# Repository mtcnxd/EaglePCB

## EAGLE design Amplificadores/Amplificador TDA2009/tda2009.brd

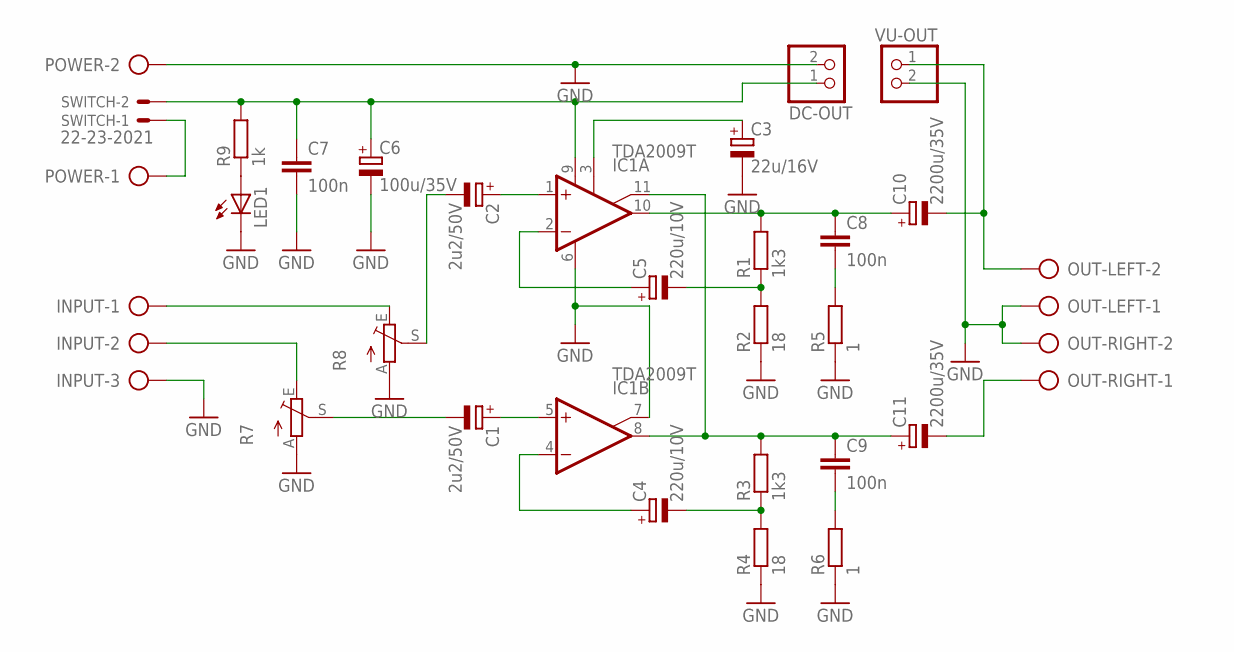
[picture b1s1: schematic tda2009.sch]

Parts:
C1, C2: 2u2/50V; E2,5-5
C3: 22u/16V; E2,5-5
C4, C5: 220u/10V; E2,5-6
C6: 100u/35V; E3,5-8
C7, C8, C9: 100n; C025-025X050
C10, C11: 2200u/35V; E7,5-16
DC-OUT: PINHD-1X2; 1X02
IC1: TDA2009T; SIP11
INPUT: AK300/3
LED1: LED5MM
OUT-LEFT: AK300/2
OUT-RIGHT: AK300/2
POWER: AK300/2
R1, R3: 1k3; 0207/10
R2, R4: 18; 0207/10
R5, R6: 1; 0207/10
R7, R8: TRIM_EU-RJ9W; RJ9W
R9: 1k; 0207/10
SWITCH: 22-23-2021
VU-OUT: PINHD-1X2; 1X02

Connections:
GND: C3.-, C6.-, C7.2, DC-OUT.2, IC1.6 (GND), IC1.7 (BTSP), INPUT.3, LED1.K (C), OUT-LEFT.1, OUT-RIGHT.2, POWER.2, R2.1, R4.1, R5.1, R6.1, R7.A, R8.A, VU-OUT.2
unnamed: C5.-, R1.1, R2.2
unnamed: C4.-, R3.1, R4.2
unnamed: C8.2, R5.2
unnamed: C9.2, R6.2
unnamed: C9.1, C11.+, IC1.8 (OUT), IC1.11 (BTSP), R3.2
unnamed: C8.1, C10.+, IC1.10 (OUT), R1.2
unnamed: C1.+, IC1.5 (+IN)
unnamed: C2.+, IC1.1 (+IN)
unnamed: INPUT.2, R7.E
unnamed: C3.+, IC1.3 (SVRR)
unnamed: C5.+, IC1.2 (-IN)
unnamed: C4.+, IC1.4 (-IN)
unnamed: INPUT.1, R8.E
unnamed: C1.-, R7.S
unnamed: C10.-, OUT-LEFT.2, VU-OUT.1
unnamed: C11.-, OUT-RIGHT.1
unnamed: C2.-, R8.S
unnamed: LED1.A, R9.1
unnamed: POWER.1, SWITCH.1
unnamed: C6.+, C7.1, DC-OUT.1, IC1.9 (V+), R9.2, SWITCH.2

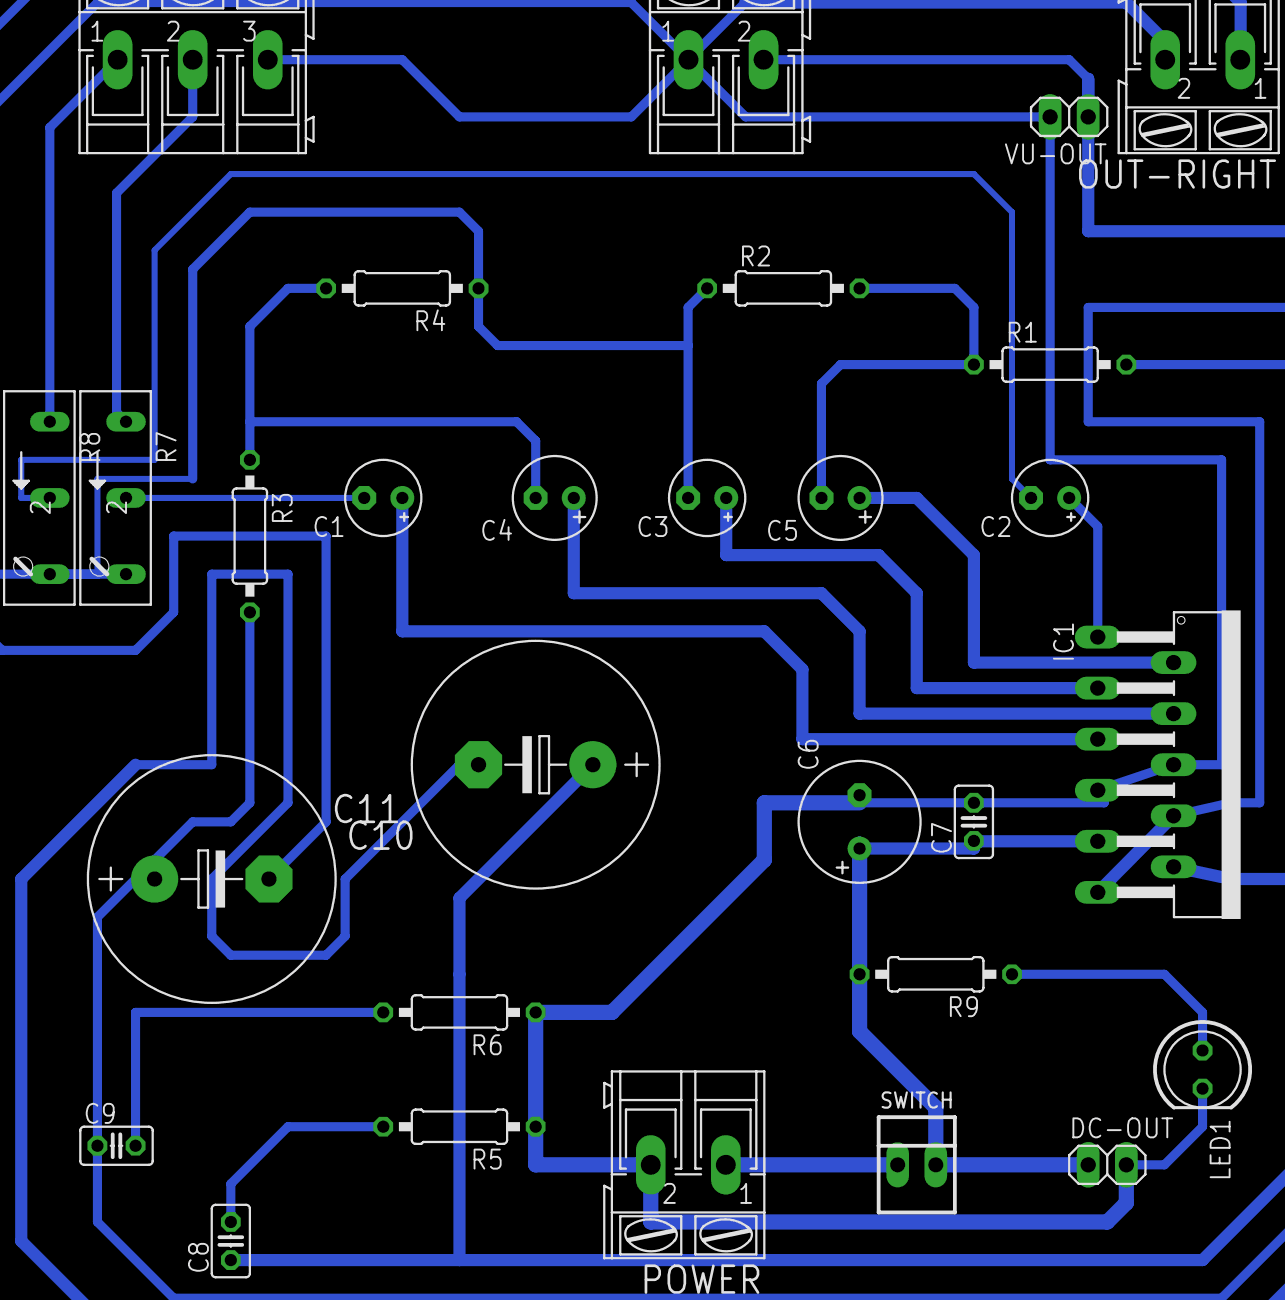
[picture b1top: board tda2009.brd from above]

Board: 2 copper layers, 29 parts (0 on the bottom side), 21 nets.

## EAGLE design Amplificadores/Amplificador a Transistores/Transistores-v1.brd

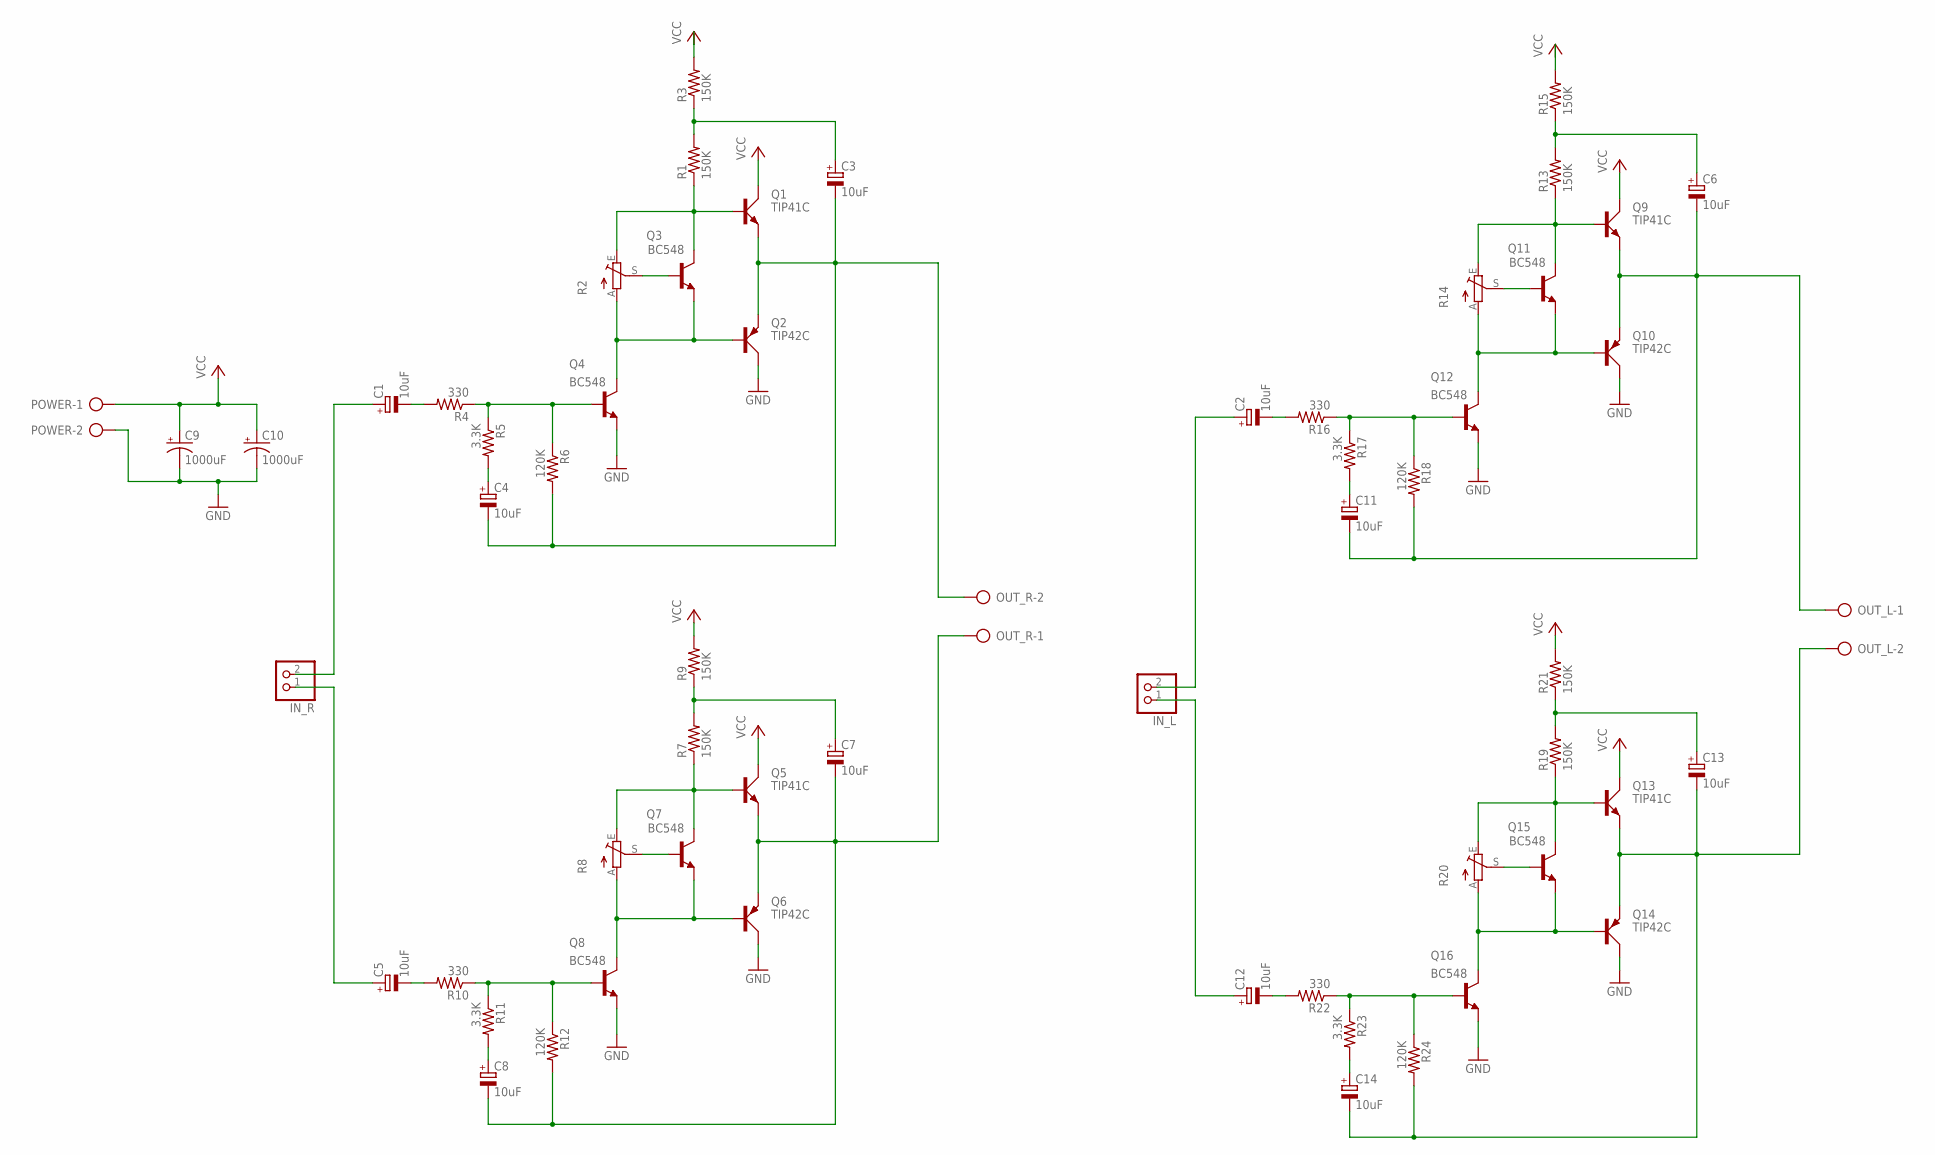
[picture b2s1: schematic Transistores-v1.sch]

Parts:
C1, C2, C3, C4, C5, C6, C7, C8, C11, C12, C13, C14: 10uF; E2,5-5
C9, C10: 1000uF; E2,5-7
IN_L: PINHD-1X2; 1X02
IN_R: PINHD-1X2; 1X02
OUT_L: AK300/2
OUT_R: AK300/2
POWER: AK300/2
Q1, Q5, Q9, Q13: TIP41C; TO220AV
Q2, Q6, Q10, Q14: TIP42C; TO220AV
Q3, Q4, Q7, Q8, Q11, Q12, Q15, Q16: BC548; TO92-EBC
R1, R3, R7, R9, R13, R15, R19, R21: 150K; 0204/7
R2, R8, R14, R20: TRIM_EU-LI10; LI10
R4, R10, R16, R22: 330; 0204/7
R5, R11, R17, R23: 3.3K; 0204/7
R6, R12, R18, R24: 120K; 0204/7

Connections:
GND: C9.-, C10.-, POWER.2, Q2.C, Q4.E, Q6.C, Q8.E, Q10.C, Q12.E, Q14.C, Q16.E
unnamed: Q3.B, R2.S
unnamed: Q1.B, Q3.C, R1.1, R2.E
unnamed: Q2.B, Q3.E, Q4.C, R2.A
unnamed: Q7.B, R8.S
unnamed: C1.+, IN_R.2
unnamed: C3.+, R1.2, R3.1
unnamed: Q4.B, R4.1, R5.1, R6.1
unnamed: C1.-, R4.2
unnamed: C4.+, R5.2
unnamed: C3.-, C4.-, OUT_R.2, Q1.E, Q2.E, R6.2
unnamed: Q5.B, Q7.C, R7.1, R8.E
unnamed: Q6.B, Q7.E, Q8.C, R8.A
unnamed: C7.+, R7.2, R9.1
unnamed: C5.+, IN_R.1
unnamed: Q8.B, R10.1, R11.1, R12.1
unnamed: C5.-, R10.2
unnamed: C8.+, R11.2
unnamed: C7.-, C8.-, OUT_R.1, Q5.E, Q6.E, R12.2
unnamed: Q11.B, R14.S
unnamed: Q9.B, Q11.C, R13.1, R14.E
unnamed: Q10.B, Q11.E, Q12.C, R14.A
unnamed: C6.+, R13.2, R15.1
unnamed: Q12.B, R16.1, R17.1, R18.1
unnamed: C2.-, R16.2
unnamed: C11.+, R17.2
unnamed: C6.-, C11.-, OUT_L.1, Q9.E, Q10.E, R18.2
unnamed: Q15.B, R20.S
unnamed: Q13.B, Q15.C, R19.1, R20.E
unnamed: Q14.B, Q15.E, Q16.C, R20.A
unnamed: C13.+, R19.2, R21.1
unnamed: Q16.B, R22.1, R23.1, R24.1
unnamed: C12.-, R22.2
unnamed: C14.+, R23.2
unnamed: C13.-, C14.-, OUT_L.2, Q13.E, Q14.E, R24.2
unnamed: C2.+, IN_L.2
unnamed: C12.+, IN_L.1
VCC: C9.+, C10.+, POWER.1, Q1.C, Q5.C, Q9.C, Q13.C, R3.2, R9.2, R15.2, R21.2

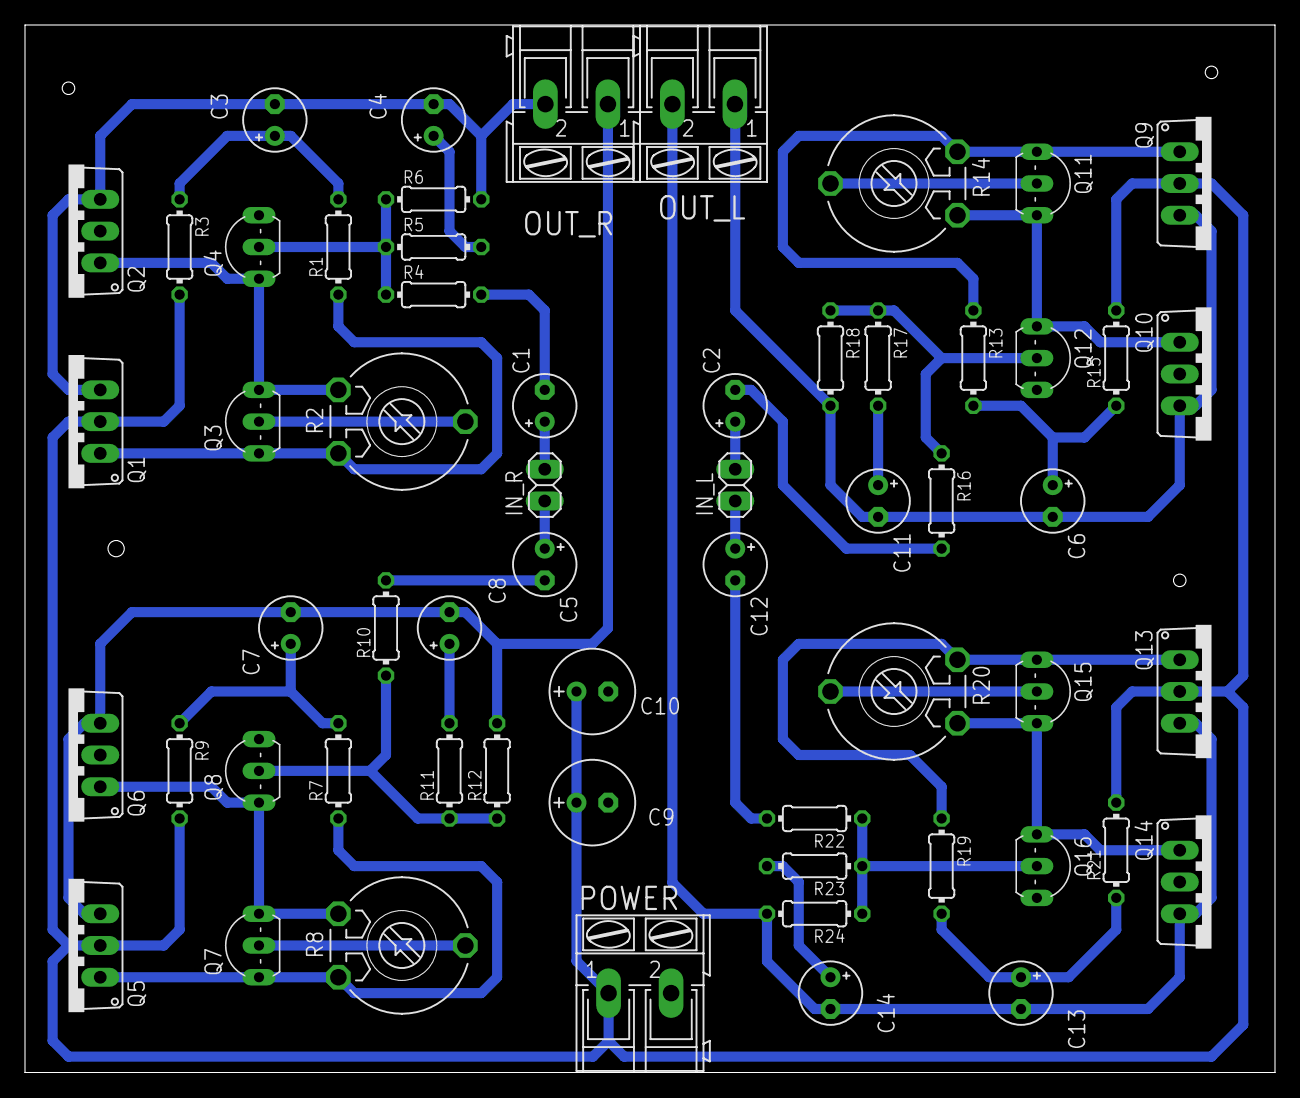
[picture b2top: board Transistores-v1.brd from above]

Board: 2 copper layers, 100.0 x 83.8 mm, 59 parts (0 on the bottom side), 38 nets.

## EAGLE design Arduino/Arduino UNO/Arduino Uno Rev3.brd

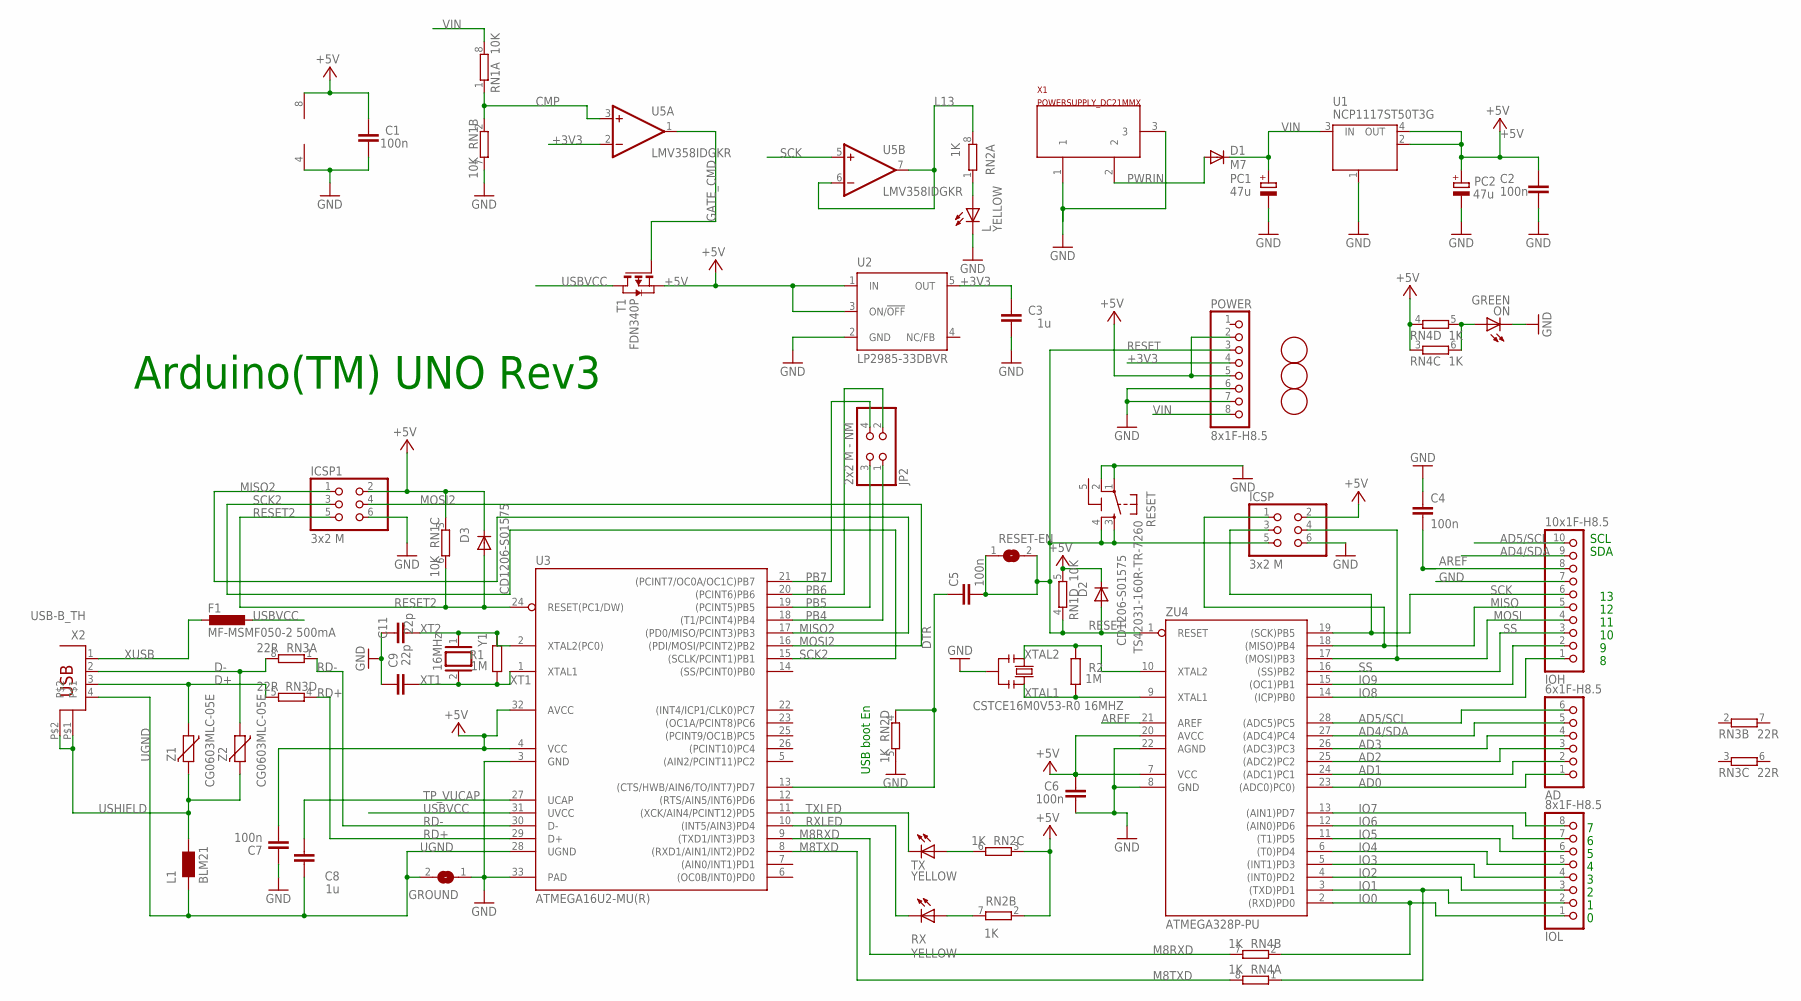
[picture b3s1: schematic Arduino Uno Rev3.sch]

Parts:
AD: 6x1F-H8.5; 1X06
C1, C2, C4, C5, C6, C7: 100n; C0603-ROUND
C3, C8: 1u; C0603-ROUND
C9, C11: 22p; C0603-ROUND
D1: M7; SMB
D2, D3: CD1206-S01575; MINIMELF
F1: MF-MSMF050-2 500mA; L1812
FD1, FD2, FD3: FIDUCIALMOUNT; FIDUCIA-MOUNT
GROUND: SJ
ICSP, ICSP1: 3x2 M; 2X03
IOH: 10x1F-H8.5; 1X10
IOL: 8x1F-H8.5; 1X08
JP2: 2x2 M - NM; 2X02
L: YELLOW; CHIP-LED0805
L1: BLM21; 0805
ON: GREEN; CHIP-LED0805
PC1, PC2: 47u; PANASONIC_D
POWER: 8x1F-H8.5; 1X08
R1, R2: 1M; R0603-ROUND
RESET: TS42031-160R-TR-7260; TS42
RESET-EN: SJ
RN1: 10K; CAY16
RN2, RN4: 1K; CAY16
RN3: 22R; CAY16
RX: YELLOW; CHIP-LED0805
T1: FDN340P; SOT-23
TX: YELLOW; CHIP-LED0805
U1: NCP1117ST50T3G; SOT223
U2: LP2985-33DBVR; SOT23-DBV
U3: ATMEGA16U2-MU(R); MLF32
U5: LMV358IDGKR; MSOP08
X1: POWERSUPPLY_DC21MMX; POWERSUPPLY_DC-21MM
X2: USB-B_TH; PN61729
Y1: 16MHz; QS
Y2: CSTCE16M0V53-R0 16MHZ; RESONATOR
Z1, Z2: CG0603MLC-05E; CT/CN0603
ZU4: ATMEGA328P-PU; DIL28-3

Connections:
5-GND: RESET.5 (5-GND)
+3V3: C3.2, POWER.4, U2.5 (OUT), U5.2 (-IN)
+5V: C1.2, C2.2, C6.2, C7.1, D2.C, D3.C, ICSP.2, ICSP1.2, PC2.+, POWER.2, POWER.5, RN1.3 (1), RN1.5 (2), RN2.2 (1), RN2.3 (1), RN4.3 (1), RN4.4 (1), T1.2 (S), U1.2 (OUT), U1.4 (OUT), U2.1 (IN), U2.3 (ON/!OFF), U3.4 (VCC), U3.32 (AVCC), U5.8 (V+), ZU4.7 (VCC), ZU4.20 (AVCC)
AD0: AD.1, ZU4.23 ((ADC0)PC0))
AD1: AD.2, ZU4.24 ((ADC1)PC1)
AD2: AD.3, ZU4.25 ((ADC2)PC2)
AD3: AD.4, ZU4.26 ((ADC3)PC3)
AD4/SDA: AD.5, IOH.9, ZU4.27 ((ADC4)PC4)
AD5/SCL: AD.6, IOH.10, ZU4.28 ((ADC5)PC5)
AREF: C4.2, IOH.8, ZU4.21 (AREF)
CMP: RN1.1, RN1.2 (1), U5.3 (+IN)
D+: RN3.5 (2), X2.3, Z1.1
D-: RN3.8 (2), X2.2, Z2.1
DTR: C5.1, RN2.4 (1), U3.13 ((CTS/HWB/AIN6/TO/INT7)PD7)
GATE_CMD: T1.3 (G), U5.1 (OUT)
GND: C1.1, C2.1, C3.1, C4.1, C6.1, C7.2, C9.2, C11.2, GROUND.1, ICSP.6, ICSP1.6, IOH.7, L.C, ON.C, PC1.-, PC2.-, POWER.6, POWER.7, RESET.1, RESET.2, RN1.7 (2), RN2.5 (2), U1.1 (GND/ADJ), U2.2 (GND), U3.3 (GND), U3.33 (PAD), U5.4 (V-), X1.1, X1.3, Y2.2, ZU4.8 (GND), ZU4.22 (AGND)
IO0: IOL.1, RN4.2 (1), ZU4.2 ((RXD)PD0)
IO1: IOL.2, RN4.1, ZU4.3 ((TXD)PD1)
IO2: IOL.3, ZU4.4 ((INT0)PD2)
IO3: IOL.4, ZU4.5 ((INT1)PD3)
IO4: IOL.5, ZU4.6 ((T0)PD4)
IO5: IOL.6, ZU4.11 ((T1)PD5)
IO6: IOL.7, ZU4.12 ((AIN0)PD6)
IO7: IOL.8, ZU4.13 ((AIN1)PD7)
IO8: IOH.1, ZU4.14 ((ICP)PB0)
IO9: IOH.2, ZU4.15 ((OC1)PB1)
L13: RN2.8 (2), U5.6 (-IN), U5.7 (OUT)
M8RXD: RN4.7 (2), U3.9 ((TXD1/INT3)PD3)
M8TXD: RN4.8 (2), U3.8 ((RXD1/AIN1/INT2)PD2)
MISO: ICSP.1, IOH.5, ZU4.18 ((MISO)PB4)
MISO2: ICSP1.1, U3.17 ((PD0/MISO/PCINT3)PB3)
MOSI: ICSP.4, IOH.4, ZU4.17 ((MOSI)PB3)
MOSI2: ICSP1.4, U3.16 ((PDI/MOSI/PCINT2)PB2)
unnamed: L.A, RN2.1
unnamed: ON.A, RN4.5 (2), RN4.6 (2)
unnamed: RN2.7 (2), RX.A
unnamed: RN2.6 (2), TX.A
PB4: JP2.1, U3.18 ((T1/PCINT4)PB4)
PB5: JP2.3, U3.19 ((PCINT5)PB5)
PB6: JP2.2, U3.20 ((PCINT6)PB6)
PB7: JP2.4, U3.21 ((PCINT7/OC0A/OC1C)PB7)
PWRIN: D1.A, X1.2
RD+: RN3.4 (1), U3.29 (D+)
RD-: RN3.1, U3.30 (D-)
RESET: C5.2, D2.A, ICSP.5, POWER.3, RESET.3, RESET.4, RESET-EN.1, RESET-EN.2, RN1.4 (1), ZU4.1 (RESET)
RESET2: D3.A, ICSP1.5, RN1.6 (2), U3.24 (RESET(PC1/DW))
RXLED: RX.C, U3.10 ((INT5/AIN3)PD4)
SCK: ICSP.3, IOH.6, U5.5 (+IN), ZU4.19 ((SCK)PB5)
SCK2: ICSP1.3, U3.15 ((SCLK/PCINT1)PB1)
SS: IOH.3, ZU4.16 ((SS)PB2)
TP_VUCAP: C8.1, U3.27 (UCAP)
TXLED: TX.C, U3.11 ((XCK/AIN4/PCINT12)PD5)
UGND: C8.2, GROUND.2, L1.1, U3.28 (UGND), X2.4
USBVCC: F1.1, T1.1 (D), U3.31 (UVCC)
USHIELD: L1.2, X2.P$1, X2.P$2, Z1.2, Z2.2
VIN: D1.C, PC1.+, POWER.8, RN1.8 (2), U1.3 (IN)
XT1: C9.1, R1.1, U3.1 (XTAL1), Y1.2
XT2: C11.1, R1.2, U3.2 (XTAL2(PC0)), Y1.1
XTAL1: R2.1, Y2.3, ZU4.9 (XTAL1)
XTAL2: R2.2, Y2.1, ZU4.10 (XTAL2)
XUSB: F1.2, X2.1

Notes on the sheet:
Arduino(TM) UNO Rev3
USB boot En
SDA
SCL

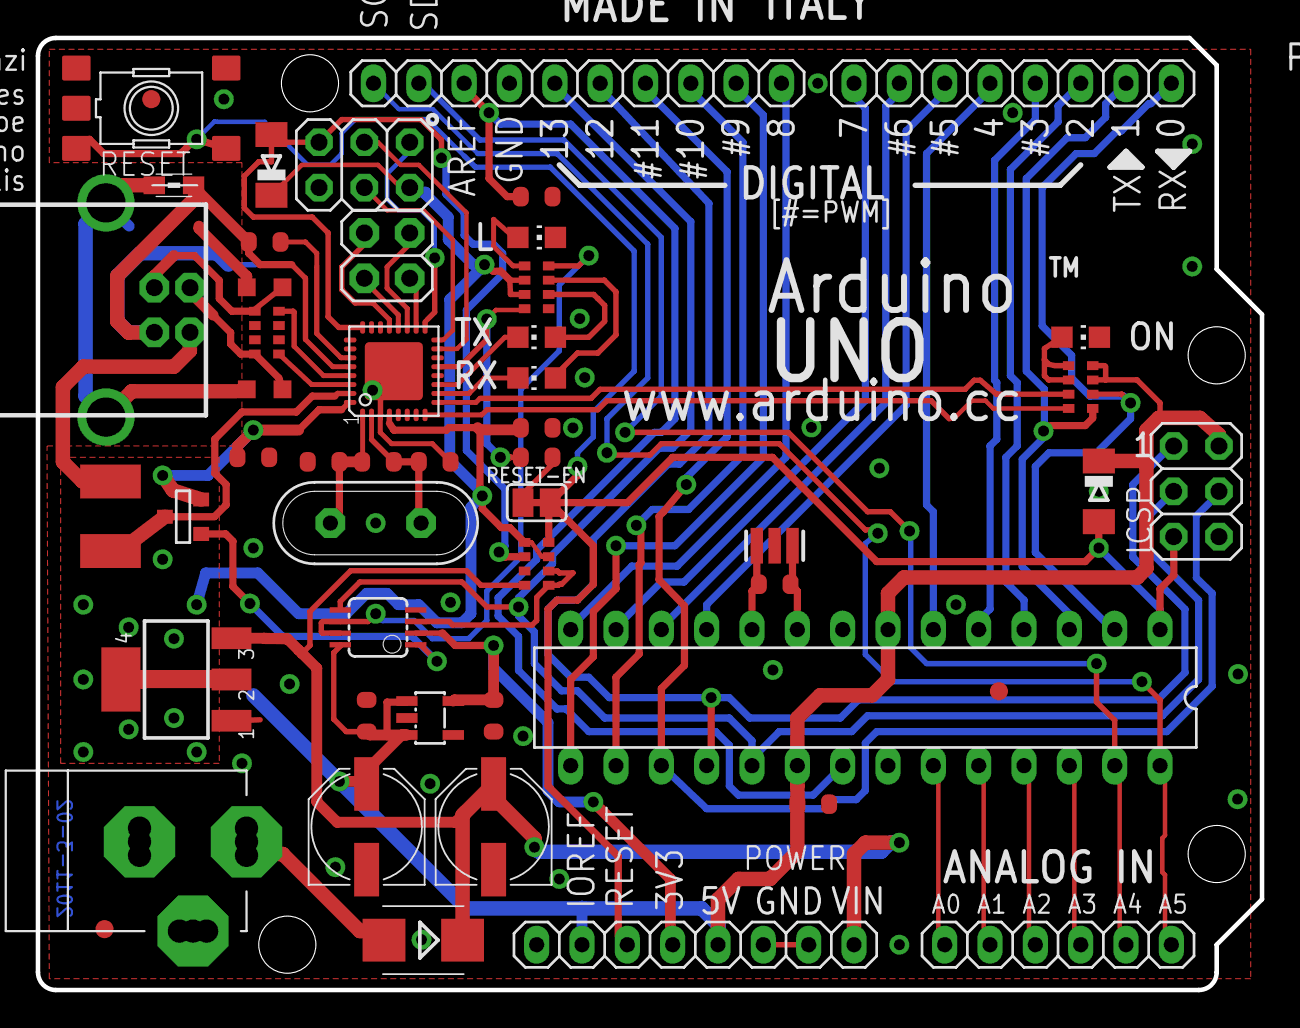
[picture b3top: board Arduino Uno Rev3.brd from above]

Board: 2 copper layers, 68.6 x 53.3 mm, 52 parts (1 on the bottom side), 60 nets.

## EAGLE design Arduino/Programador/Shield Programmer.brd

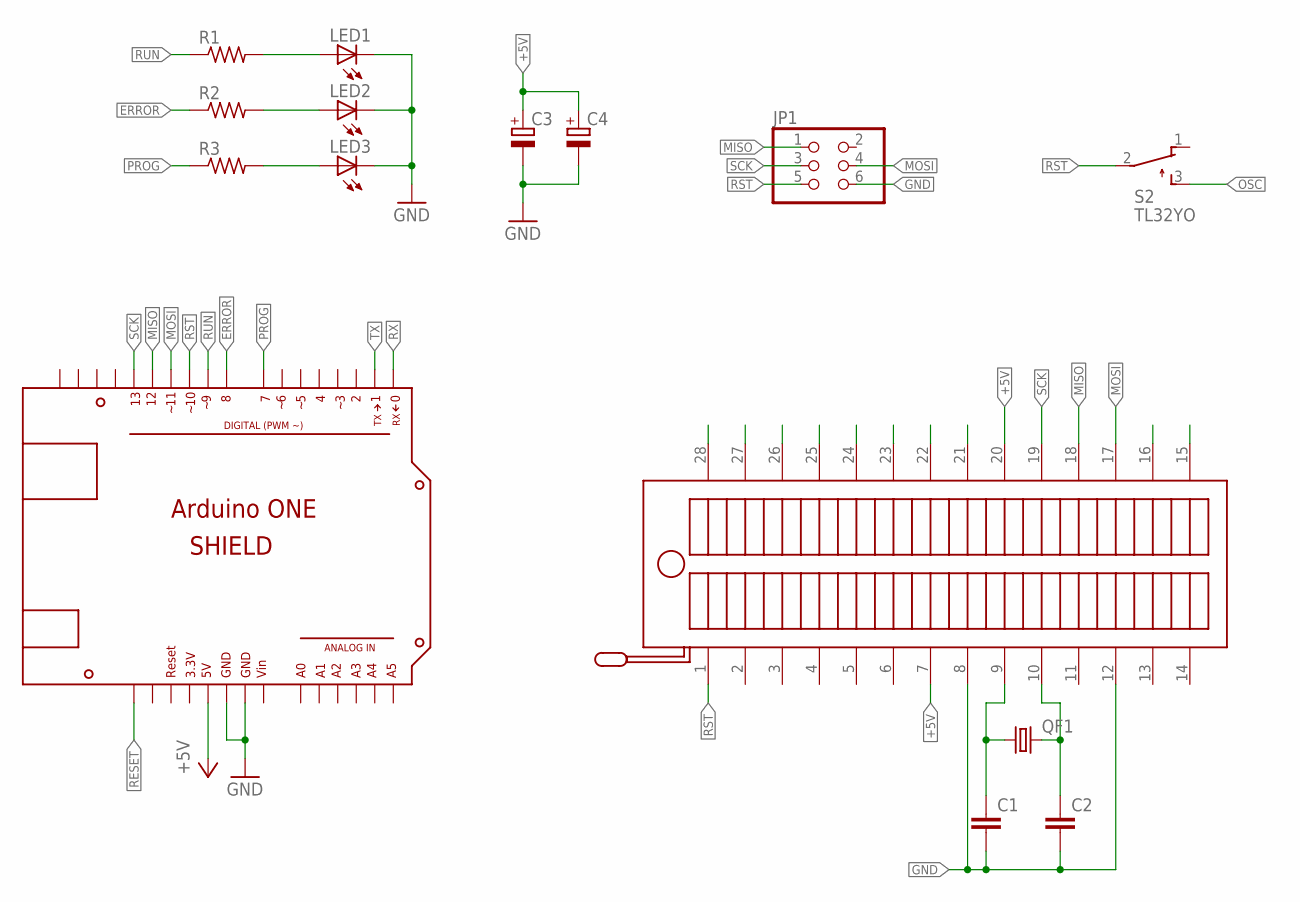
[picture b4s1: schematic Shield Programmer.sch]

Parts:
C1, C2: C5/2.5; C5B2.5
C3, C4: CPOL-EUE2.5-7; E2,5-7
JP1: PINHD-2X3; 2X03
LED1, LED2, LED3: LED3MM
QF1: CRYSTALHC49U-V; HC49U-V
R1, R2, R3: R-US_0204/7; 0204/7
S2: TL32YO; TL3XYO
U$2: ZIF-28
U$3: SHIELD

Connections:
+5V: C3.+, C4.+, U$2.7 (PIN7), U$2.20 (PIN20), U$3.5V
ERROR: R2.1, U$3.8
GND: C1.2, C2.2, C3.-, C4.-, JP1.6, LED1.K (C), LED2.K (C), LED3.K (C), U$2.8 (PIN8), U$2.12 (PIN12), U$3.GND1, U$3.GND2
MISO: JP1.1, U$2.18 (PIN18), U$3.12
MOSI: JP1.4, U$2.17 (PIN17), U$3.11
unnamed: LED3.A, R3.2
unnamed: LED2.A, R2.2
unnamed: LED1.A, R1.2
unnamed: C2.1, QF1.2, U$2.10 (PIN10)
OSC: C1.1, QF1.1, S2.3 (S), U$2.9 (PIN9)
PROG: R3.1, U$3.7
RESET: U$3.NONE
RST: JP1.5, S2.2, U$2.1 (PIN1), U$3.10
RUN: R1.1, U$3.9
RX: U$3.0
SCK: JP1.3, U$2.19 (PIN19), U$3.13
TX: U$3.1

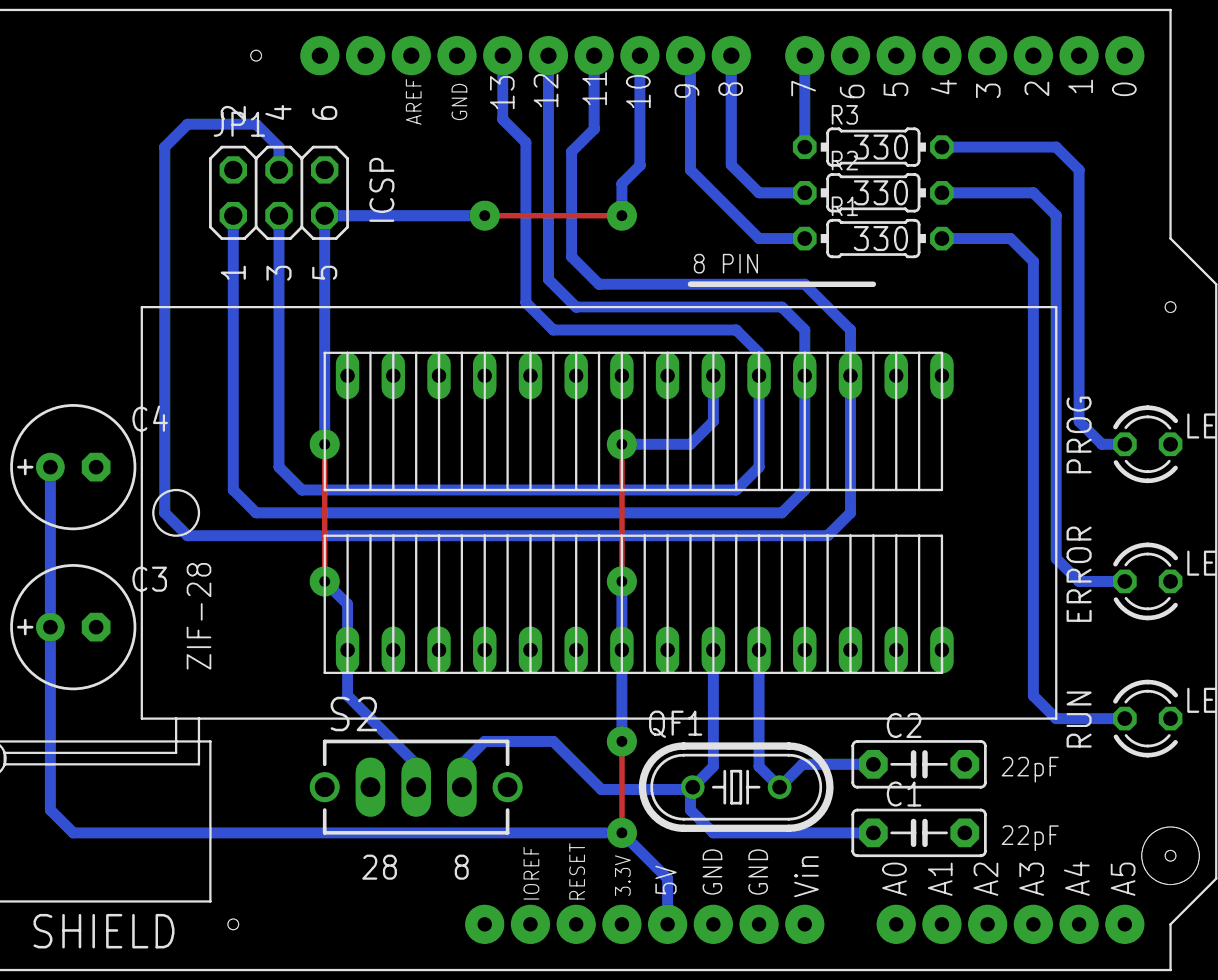
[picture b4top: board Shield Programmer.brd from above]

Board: 2 copper layers, 15 parts (0 on the bottom side), 14 nets.

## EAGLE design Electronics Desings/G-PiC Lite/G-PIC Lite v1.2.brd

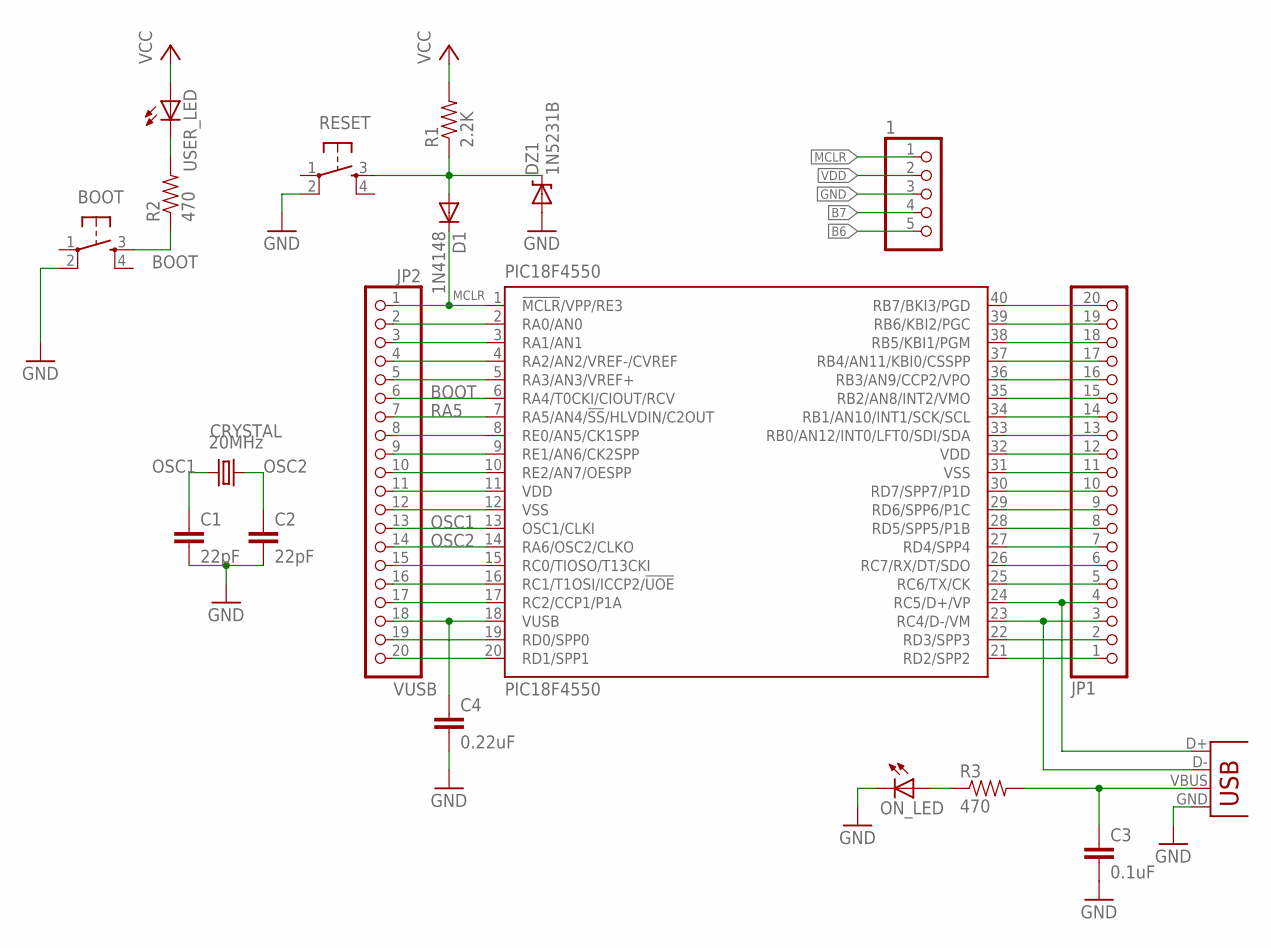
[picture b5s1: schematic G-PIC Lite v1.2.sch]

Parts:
1: PINHD-1X5; 1X05
BOOT: TAC_SWITCHPTH; TACTILE-PTH
C1, C2: 22pF; C5B3
C3: 0.1uF; C2.5-3
C4: 0.22uF; C5B3
CRYSTAL: 20MHz; HC49US
D1: 1N4148; D-5
DZ1: 1N5231B; DIODE-ZENER
JP1, JP2: PINHD-1X20; 1X20
ON_LED: LED3MM
PIC18F4550: PIC18F4550; DIL40
R1: 2.2K; AXIAL-0.4
R2, R3: 470; AXIAL-0.4
RESET: TAC_SWITCHPTH; TACTILE-PTH
USB: X1; USB-B-PTH
USER_LED: LED3MM

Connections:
B6: 1.5, JP1.19, PIC18F4550.39 (RB6/KBI2/PGC)
B7: 1.4, JP1.20, PIC18F4550.40 (RB7/BKI3/PGD)
BOOT: BOOT.3, JP2.6, PIC18F4550.6 (RA4/T0CKI/CIOUT/RCV), R2.P$1 (1)
D+: JP1.4, PIC18F4550.24 (RC5/D+/VP), USB.D+
D-: JP1.3, PIC18F4550.23 (RC4/D-/VM), USB.D-
GND: 1.3, BOOT.2, C1.2, C2.2, C3.2, C4.2, DZ1.P$2 (A), JP1.11, JP2.12, ON_LED.K (C), PIC18F4550.12 (VSS), PIC18F4550.31 (VSS), RESET.2, USB.GND
MCLR: 1.1, D1.C, JP2.1, PIC18F4550.1 (!MCLR!/VPP/RE3)
unnamed: JP1.1, PIC18F4550.21 (RD2/SPP2)
unnamed: JP1.2, PIC18F4550.22 (RD3/SPP3)
unnamed: R2.P$2 (2), USER_LED.K (C)
unnamed: JP1.5, PIC18F4550.25 (RC6/TX/CK)
unnamed: JP1.6, PIC18F4550.26 (RC7/RX/DT/SDO)
unnamed: JP1.7, PIC18F4550.27 (RD4/SPP4)
unnamed: JP1.8, PIC18F4550.28 (RD5/SPP5/P1B)
unnamed: JP1.9, PIC18F4550.29 (RD6/SPP6/P1C)
unnamed: JP1.10, PIC18F4550.30 (RD7/SPP7/P1D)
unnamed: ON_LED.A, R3.P$1 (1)
unnamed: JP1.13, PIC18F4550.33 (RB0/AN12/INT0/LFT0/SDI/SDA)
unnamed: JP1.14, PIC18F4550.34 (RB1/AN10/INT1/SCK/SCL)
unnamed: JP1.15, PIC18F4550.35 (RB2/AN8/INT2/VMO)
unnamed: JP1.16, PIC18F4550.36 (RB3/AN9/CCP2/VPO)
unnamed: JP1.17, PIC18F4550.37 (RB4/AN11/KBI0/CSSPP)
unnamed: JP1.18, PIC18F4550.38 (RB5/KBI1/PGM)
unnamed: D1.A, DZ1.P$1 (C), R1.P$1 (1), RESET.3
unnamed: JP2.2, PIC18F4550.2 (RA0/AN0)
unnamed: JP2.3, PIC18F4550.3 (RA1/AN1)
unnamed: JP2.4, PIC18F4550.4 (RA2/AN2/VREF-/CVREF)
unnamed: JP2.5, PIC18F4550.5 (RA3/AN3/VREF+)
unnamed: JP2.8, PIC18F4550.8 (RE0/AN5/CK1SPP)
unnamed: JP2.9, PIC18F4550.9 (RE1/AN6/CK2SPP)
unnamed: JP2.10, PIC18F4550.10 (RE2/AN7/OESPP)
unnamed: JP2.15, PIC18F4550.15 (RC0/TIOSO/T13CKI)
unnamed: JP2.16, PIC18F4550.16 (RC1/T1OSI/ICCP2/!UOE)
unnamed: JP2.17, PIC18F4550.17 (RC2/CCP1/P1A)
unnamed: JP2.19, PIC18F4550.19 (RD0/SPP0)
unnamed: JP2.20, PIC18F4550.20 (RD1/SPP1)
OSC1: C1.1, CRYSTAL.2, JP2.13, PIC18F4550.13 (OSC1/CLKI)
OSC2: C2.1, CRYSTAL.1, JP2.14, PIC18F4550.14 (RA6/OSC2/CLKO)
RA5: JP2.7, PIC18F4550.7 (RA5/AN4/!SS!/HLVDIN/C2OUT)
VDD: 1.2, C3.1, JP1.12, JP2.11, PIC18F4550.11 (VDD), PIC18F4550.32 (VDD), R1.P$2 (2), R3.P$2 (2), USB.VBUS, USER_LED.A
VUSB: C4.1, JP2.18, PIC18F4550.18 (VUSB)

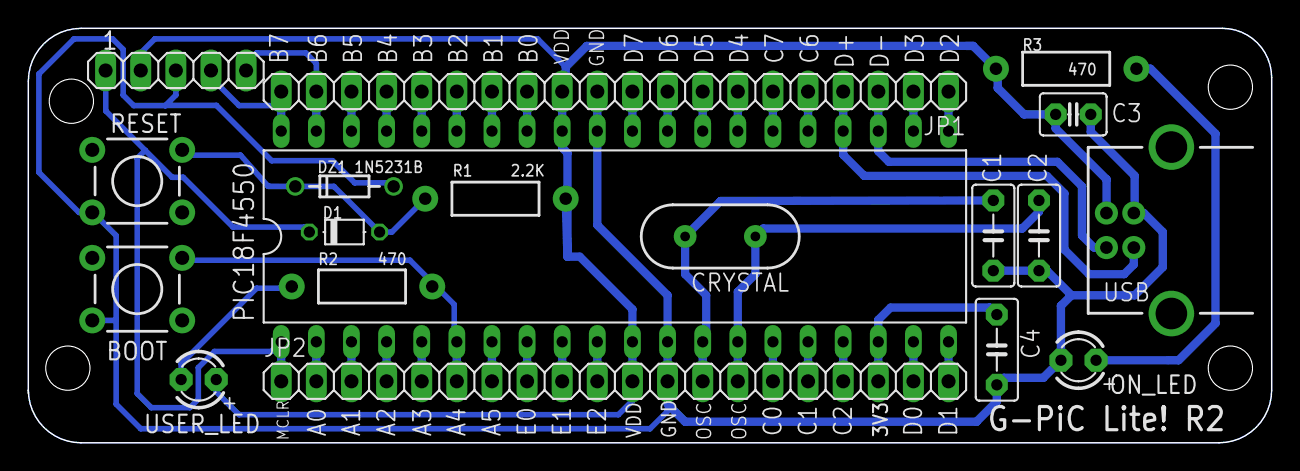
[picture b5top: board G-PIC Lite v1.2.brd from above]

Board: 2 copper layers, 89.9 x 30.0 mm, 19 parts (0 on the bottom side), 41 nets.

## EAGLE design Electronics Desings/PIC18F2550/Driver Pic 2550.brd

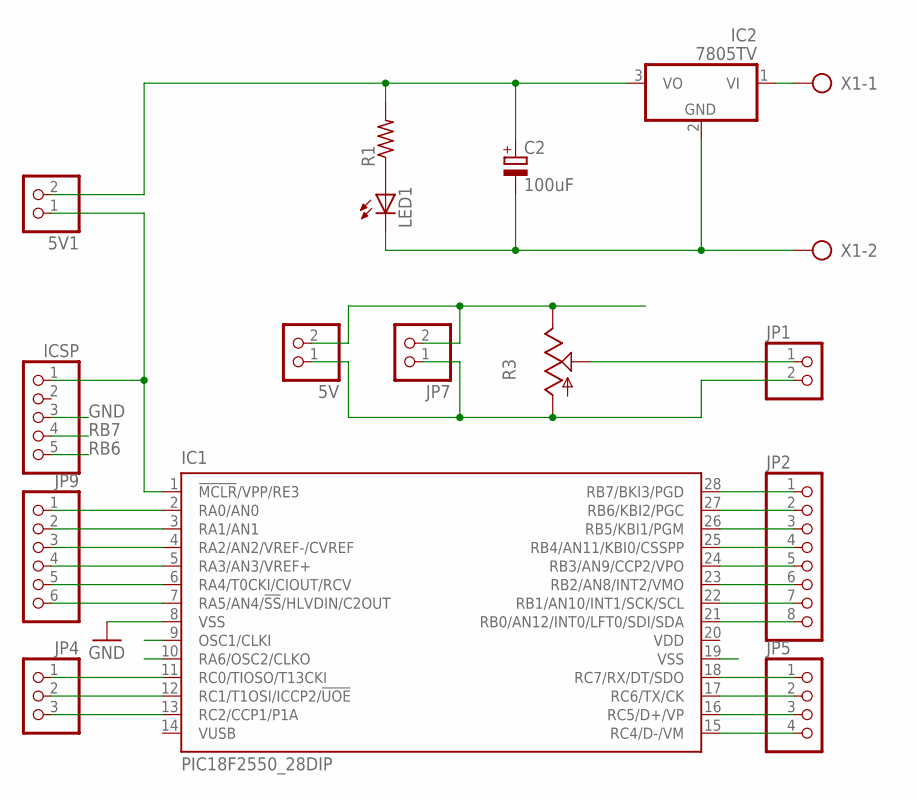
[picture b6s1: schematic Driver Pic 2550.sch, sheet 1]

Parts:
5V, 5V1: PINHD-1X2; 1X02
C2: 100uF; E2,5-6E
IC1: PIC18F2550_28DIP; DIL28-3
IC2: 7805TV; TO220V
ICSP: PINHD-1X5/90; 1X05/90
JP1, JP7: PINHD-1X2; 1X02
JP2: PINHD-1X8; 1X08
JP4: PINHD-1X3; 1X03
JP5: PINHD-1X4; 1X04
JP9: PINHD-1X6; 1X06
LED1: LED3MM
R1: R-US_0207/2V; 0207/2V
R3: TRIM_US-B64W; B64W
X1: AK300/2

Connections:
AN0: IC1.2 (RA0/AN0), JP9.1; also elsewhere on the board
D+: IC1.16 (RC5/D+/VP), JP5.3
D-: IC1.15 (RC4/D-/VM), JP5.4
GND: 5V.1, C2.-, IC1.8 (VSS), IC1.19 (VSS), IC2.2 (GND), ICSP.3, JP1.2, JP7.1, LED1.K (C), R3.A, X1.2; also elsewhere on the board
unnamed: IC1.7 (RA5/AN4/!SS!/HLVDIN/C2OUT), JP9.6
unnamed: 5V1.1, IC1.1 (!MCLR!/VPP/RE3), ICSP.1
unnamed: LED1.A, R1.1
unnamed: IC1.6 (RA4/T0CKI/CIOUT/RCV), JP9.5
unnamed: IC1.5 (RA3/AN3/VREF+), JP9.4
unnamed: IC1.4 (RA2/AN2/VREF-/CVREF), JP9.3
unnamed: IC1.26 (RB5/KBI1/PGM), JP2.3
unnamed: IC1.25 (RB4/AN11/KBI0/CSSPP), JP2.4
unnamed: IC1.24 (RB3/AN9/CCP2/VPO), JP2.5
unnamed: JP1.1, R3.S
unnamed: IC1.3 (RA1/AN1), JP9.2
unnamed: IC1.13 (RC2/CCP1/P1A), JP4.3
unnamed: IC1.11 (RC0/TIOSO/T13CKI), JP4.1
unnamed: IC1.12 (RC1/T1OSI/ICCP2/!UOE), JP4.2
unnamed: IC2.1 (VI), X1.1
unnamed: IC1.18 (RC7/RX/DT/SDO), JP5.1
unnamed: IC1.17 (RC6/TX/CK), JP5.2
OSC1: IC1.9 (OSC1/CLKI)
OSC2: IC1.10 (RA6/OSC2/CLKO)
RB0: IC1.21 (RB0/AN12/INT0/LFT0/SDI/SDA), JP2.8
RB1: IC1.22 (RB1/AN10/INT1/SCK/SCL), JP2.7
RB2: IC1.23 (RB2/AN8/INT2/VMO), JP2.6
RB6: IC1.27 (RB6/KBI2/PGC), ICSP.5, JP2.2
RB7: IC1.28 (RB7/BKI3/PGD), ICSP.4, JP2.1
VDD: 5V.2, 5V1.2, C2.+, IC1.20 (VDD), IC2.3 (VO), JP7.2, R1.2, R3.E; also elsewhere on the board

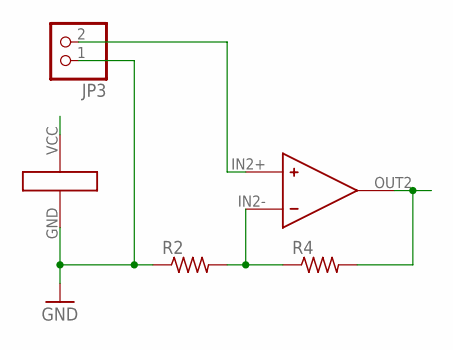
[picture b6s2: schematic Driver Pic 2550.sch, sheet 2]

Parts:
JP3: PINHD-1X2; 1X02
R2, R4: R-US_0204/7; 0204/7
U$1: LM358

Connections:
AN0: R4.2, U$1.OUT2 (OUT); also elsewhere on the board
GND: JP3.1, R2.1, U$1.GND; also elsewhere on the board
unnamed: JP3.2, U$1.IN2+ (IN+)
unnamed: R2.2, R4.1, U$1.IN2- (IN-)
VDD: U$1.VCC; also elsewhere on the board

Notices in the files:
parts and their libraries:
SparkFun-DiscreteSemi: Licensing: CC v3.0 Share-Alike You are welcome to use this library for commercial purposes.
